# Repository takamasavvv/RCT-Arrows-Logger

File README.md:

# RCT-Arrows-Logger
 Logger module for GS-8

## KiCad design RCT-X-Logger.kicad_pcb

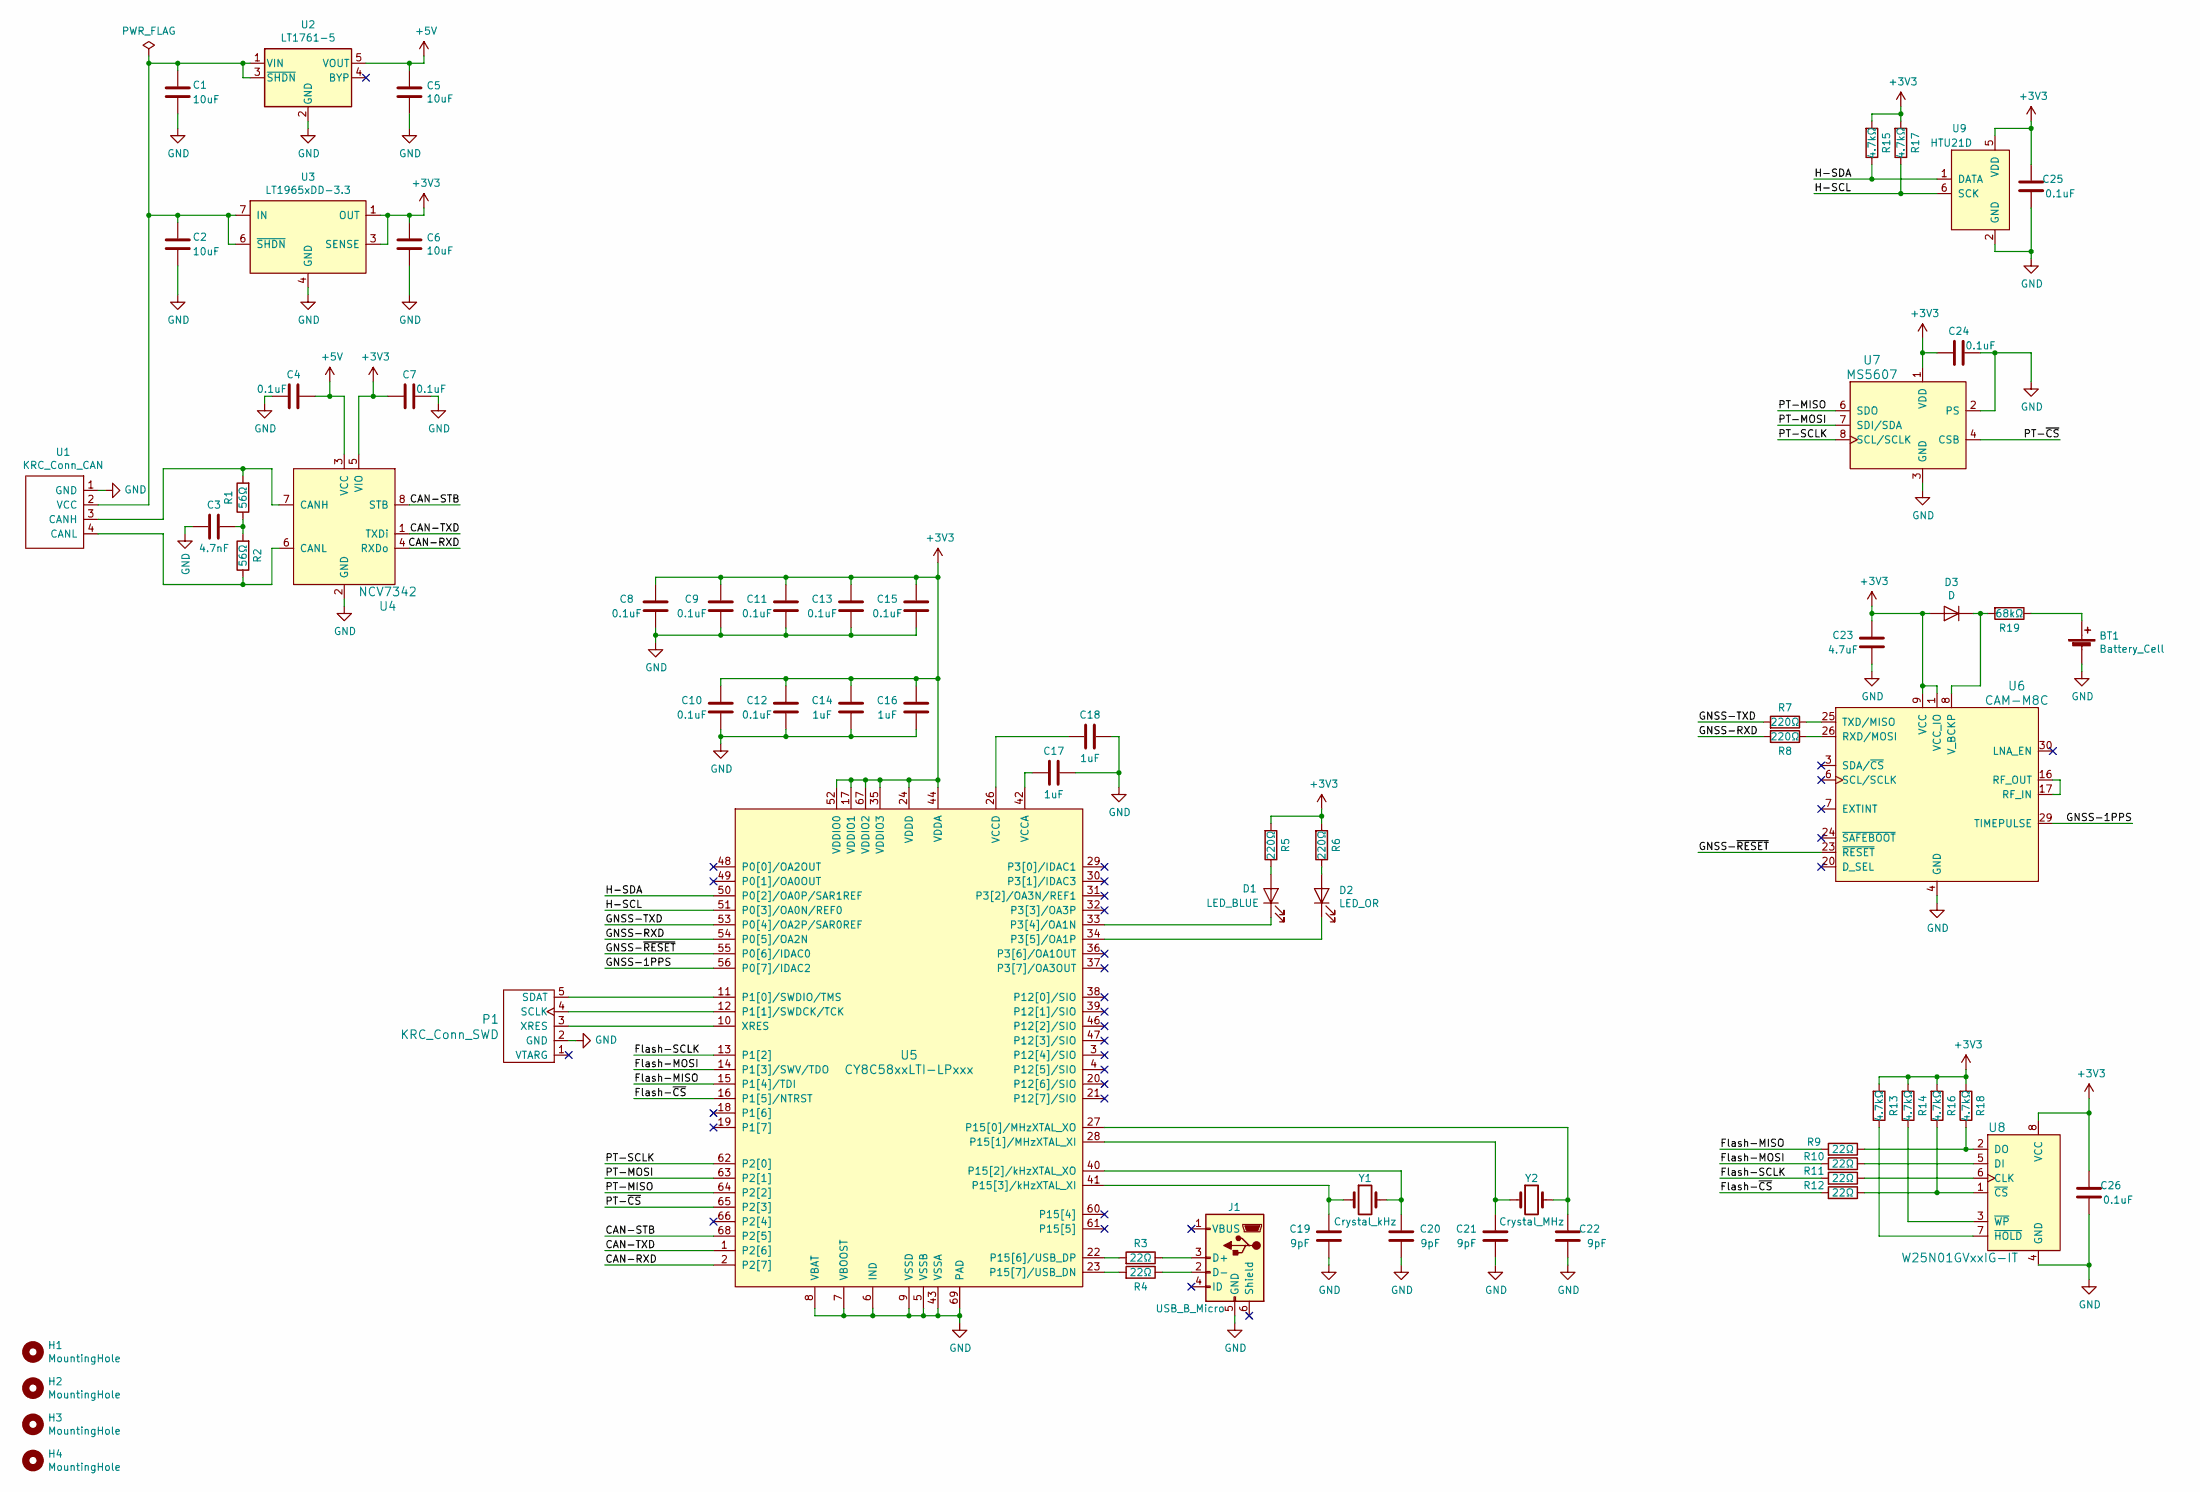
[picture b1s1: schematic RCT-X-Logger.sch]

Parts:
BT1: Battery_Cell; BatteryHolder_Seiko_MS621F; MPN MS621FE
C1, C2, C5, C6: 10uF; C_0603_1608Metric; MPN GRM188R61E106MA73D
C3: 4.7nF; C_0402_1005Metric; MPN GRM155R71H472KA01D
C4, C7, C8, C9, C10, C11, C12, C13, C15, C24, C25, C26: 0.1uF; C_0402_1005Metric; MPN GRM155R62A104KE14D
C14, C16, C17, C18: 1uF; C_0402_1005Metric; MPN GRM155R61E105KA12D
C19, C20, C21, C22: 9pF; C_0201_0603Metric; MPN GRM0335C1E9R0CA01D
C23: 4.7uF; C_0603_1608Metric; MPN GRM185R61C475ME11D
D1: LED_BLUE; LED_0603_1608Metric; MPN SMLE12BC7TT86
D2: LED_OR; LED_0603_1608Metric; MPN SML-E12D8WT86
D3: D; D_SOD-723; MPN 1SS400GT2R
H1, H2, H3, H4: MountingHole; MountingHole_3.5mm
J1: USB_B_Micro; Hirose_ZX_ZX62D-B-5P8; MPN ZX62D-B-5P8(30)
P1: KRC_Conn_SWD; JST_JQ_05JQ-BT_1x05_P2.5mm_Vertical; MPN 05JQ-BT
R1, R2: 56Ω; R_0402_1005Metric; MPN ERJ-2GEJ560X
R3, R4, R9, R10, R11, R12: 22Ω; R_0402_1005Metric; MPN ERJ-2GEJ220X
R5, R6, R7, R8: 220Ω; R_0402_1005Metric; MPN ERJ-2GEJ221X
R13, R14, R15, R16, R17, R18: 4.7kΩ; R_0402_1005Metric; MPN ERJ-2GEJ472X
R19: 68kΩ; R_0402_1005Metric; MPN ERJ-2GEJ683X
U1: KRC_Conn_CAN; JST_XH_S4B-XH-A_1x04_P2.50mm_Horizontal; MPN S4B-XH-A
U2: LT1761-5; TSOT-23-5; MPN LT1761MPS5-5#TRMPBF
U3: LT1965xDD-3.3; DFN-8-1EP_3x3mm_P0.5mm_EP1.66x2.38mm; MPN LT1965EDD-3.3#PBF
U4: NCV7342; DFN-8-1EP_3x3mm_P0.65mm_EP1.55x2.4mm; MPN NCV7342MW3R2G
U5: CY8C58xxLTI-LPxxx; Cypress_QFN-68_EP_8x8_Pitch0.4mm; MPN CY8C5868LTI-LP039
U6: CAM-M8C; ublox-CAM; MPN CAM-M8C-0-10
U7: MS5607; TE_Sensor_MS8607; MPN MS560702BA03-50
U8: W25N01GVxxIG-IT; WSON-8_8x6mm_P1.27mm; MPN W25N01GVZEIG TR
U9: HTU21D; DFN-6-1EP_3x3mm_P1mm_EP1.5x2.4mm; MPN HPP845E131R4
Y1: Crystal_kHz; Crystal_SeikoEpson_FC-135; MPN FC-135R 32.7680KF-AC3
Y2: Crystal_MHz; Crystal_Murata_XRCHA; MPN XRCHA24M000F0A01R0

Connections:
+3V3: C6.1, C7.1, C8.2, C9.2, C10.2, C11.2, C12.2, C13.2, C14.1, C15.2, C16.1, C23.2, C24.2, C25.2, C26.2, D3.2 (A), R5.2, R6.2, R13.2, R14.2, R15.2, R16.2, R17.2, R18.2, U3.1 (OUT), U3.2 (OUT), U3.3 (SENSE), U4.5 (VIO), U5.17 (VDDIO1), U5.24 (VDDD), U5.35 (VDDIO3), U5.44 (VDDA), U5.52 (VDDIO0), U5.59 (VDDD), U5.67 (VDDIO2), U6.1 (VCC_IO), U6.9 (VCC), U7.1 (VDD), U8.8 (VCC), U9.5 (VDD)
+5V: C4.1, C5.1, U2.5 (VOUT), U4.3 (VCC)
/CAN-RXD: U4.4 (RXDo), U5.2 (P2[7])
/CAN-STB: U4.8 (STB), U5.68 (P2[5])
/CAN-TXD: U4.1 (TXDi), U5.1 (P2[6])
/Flash-MISO: R9.2, U5.15 (P1[4]/TDI)
/Flash-MOSI: R10.2, U5.14 (P1[3]/SWV/TDO)
/Flash-SCLK: R11.2, U5.13 (P1[2])
/Flash-~CS: R12.2, U5.16 (P1[5]/NTRST)
/GNSS-1PPS: U5.56 (P0[7]/IDAC2), U6.29 (TIMEPULSE)
/GNSS-RXD: R8.2, U5.54 (P0[5]/OA2N)
/GNSS-TXD: R7.2, U5.53 (P0[4]/OA2P/SAR0REF)
/GNSS-~RESET: U5.55 (P0[6]/IDAC0), U6.23 (~RESET)
/H-SCL: R17.1, U5.51 (P0[3]/OA0N/REF0), U9.6 (SCK)
/H-SDA: R15.1, U5.50 (P0[2]/OA0P/SAR1REF), U9.1 (DATA)
/PT-MISO: U5.64 (P2[2]), U7.6 (SDO)
/PT-MOSI: U5.63 (P2[1]), U7.7 (SDI/SDA)
/PT-SCLK: U5.62 (P2[0]), U7.8 (SCL/SCLK)
/PT-~CS: U5.65 (P2[3]), U7.4 (CSB), U7.5 (CSB)
GND: BT1.2 (-), C1.2, C2.2, C3.2, C4.2, C5.2, C6.2, C7.2, C8.1, C9.1, C10.1, C11.1, C12.1, C13.1, C14.2, C15.1, C16.2, C17.2, C18.2, C19.1, C20.1, C21.1, C22.1, C23.1, C24.1, C25.1, C26.1, J1.5 (GND), P1.2 (GND), U1.1 (GND), U2.2 (GND), U3.4 (GND), U3.5 (GND), U3.9 (PAD), U4.2 (GND), U4.9 (PAD), U5.5 (VSSB), U5.6 (IND), U5.7 (VBOOST), U5.8 (VBAT), U5.9 (VSSD), U5.25 (VSSD), U5.43 (VSSA), U5.45 (VSSD), U5.58 (VSSD), U5.69 (PAD), U6.4 (GND), U6.5 (GND), U6.10 (GND), U6.11 (GND), U6.12 (GND), U6.13 (GND), U6.14 (GND), U6.15 (GND), U6.18 (GND), U6.19 (GND), U6.21 (GND), U6.22 (GND), U6.27 (GND), U6.31 (GND), U7.2 (PS), U7.3 (GND), U8.4 (GND), U8.9 (PAD), U9.2 (GND), U9.7 (PAD)
unnamed: BT1.1 (+), R19.1
unnamed: C1.1, C2.1, U1.2 (VCC), U2.1 (VIN), U2.3 (~SHDN), U3.6 (~SHDN), U3.7 (IN), U3.8 (IN)
unnamed: C3.1, R1.1, R2.2
unnamed: C17.1, U5.42 (VCCA)
unnamed: C18.1, U5.26 (VCCD), U5.57 (VCCD)
unnamed: C19.2, U5.41 (P15[3]/kHzXTAL_XI), Y1.1
unnamed: C20.2, U5.40 (P15[2]/kHzXTAL_XO), Y1.2
unnamed: C21.2, U5.28 (P15[1]/MHzXTAL_XI), Y2.1
unnamed: C22.2, U5.27 (P15[0]/MHzXTAL_XO), Y2.2
unnamed: D1.1 (K), U5.33 (P3[4]/OA1N)
unnamed: D1.2 (A), R5.1
unnamed: D2.1 (K), U5.34 (P3[5]/OA1P)
unnamed: D2.2 (A), R6.1
unnamed: D3.1 (K), R19.2, U6.8 (V_BCKP)
unnamed: J1.2 (D-), R4.1
unnamed: J1.3 (D+), R3.1
unnamed: P1.3 (XRES), U5.10 (XRES)
unnamed: P1.4 (SCLK), U5.12 (P1[1]/SWDCK/TCK)
unnamed: P1.5 (SDAT), U5.11 (P1[0]/SWDIO/TMS)
unnamed: R1.2, U1.3 (CANH), U4.7 (CANH)
unnamed: R2.1, U1.4 (CANL), U4.6 (CANL)
unnamed: R3.2, U5.22 (P15[6]/USB_DP)
unnamed: R4.2, U5.23 (P15[7]/USB_DN)
unnamed: R7.1, U6.25 (TXD/MISO)
unnamed: R8.1, U6.26 (RXD/MOSI)
unnamed: R10.1, U8.5 (DI)
unnamed: R11.1, U8.6 (CLK)
unnamed: R12.1, R16.1, U8.1 (~CS)
unnamed: R13.1, U8.7 (~HOLD)
unnamed: R14.1, U8.3 (~WP)
unnamed: R9.1, R18.1, U8.2 (DO)
unnamed: U6.16 (RF_OUT), U6.17 (RF_IN)

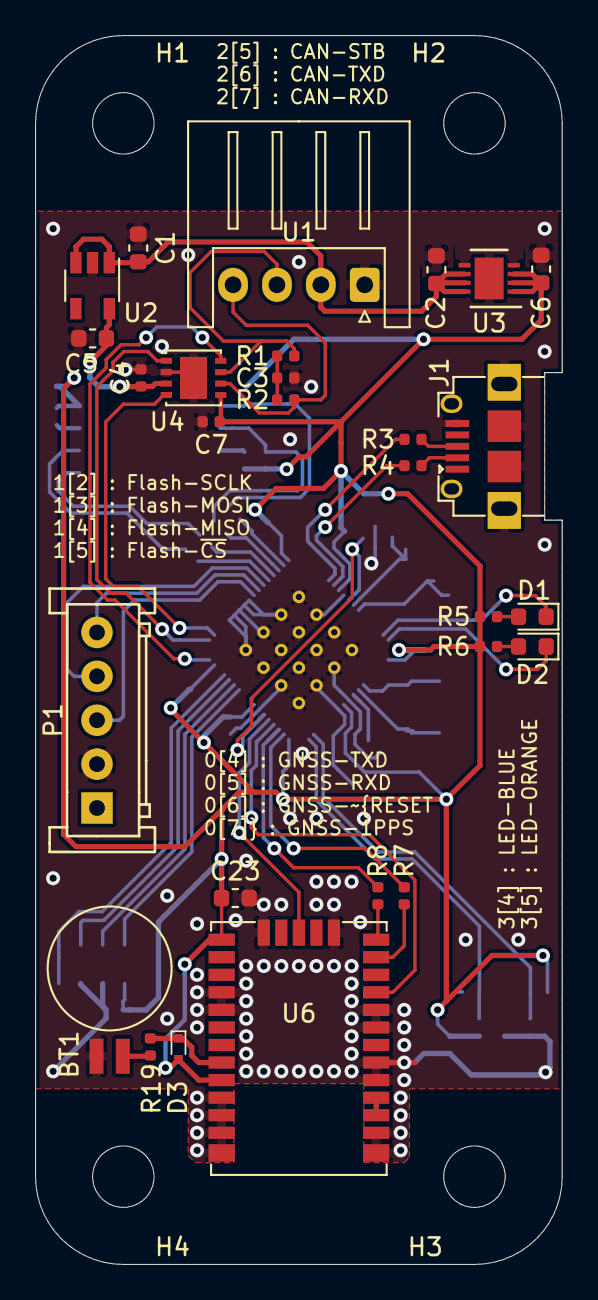
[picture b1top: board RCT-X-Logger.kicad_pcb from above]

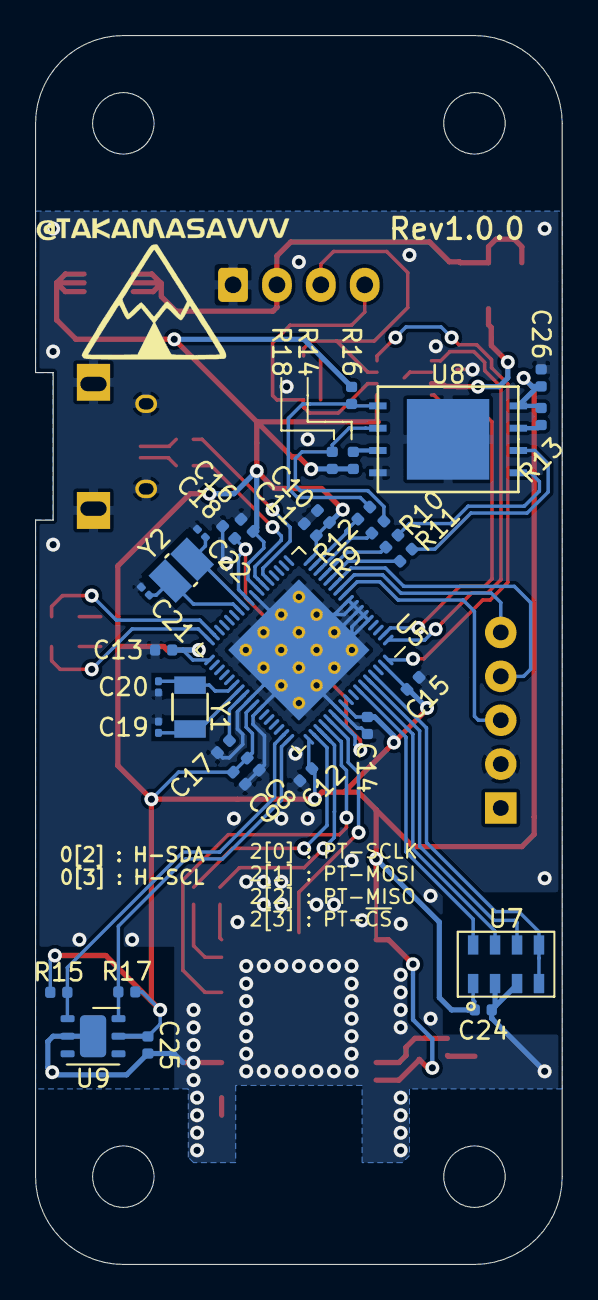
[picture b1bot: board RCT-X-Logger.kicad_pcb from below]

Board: 2 copper layers, 30.0 x 70.0 mm, 66 parts (34 on the bottom side), 52 nets.

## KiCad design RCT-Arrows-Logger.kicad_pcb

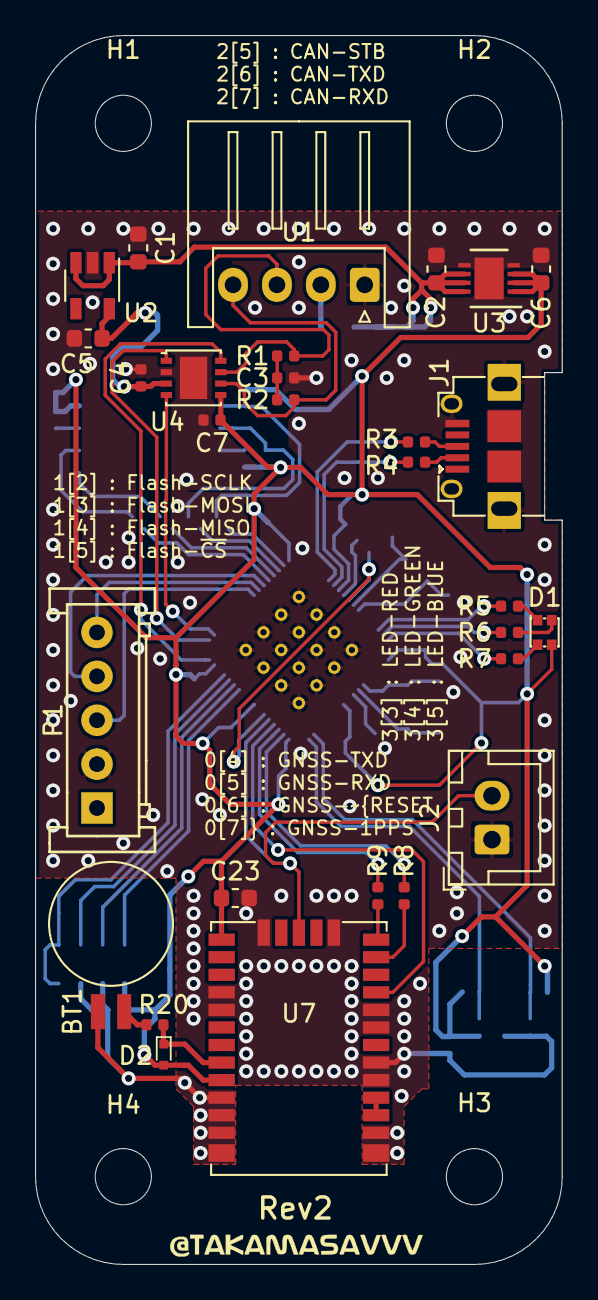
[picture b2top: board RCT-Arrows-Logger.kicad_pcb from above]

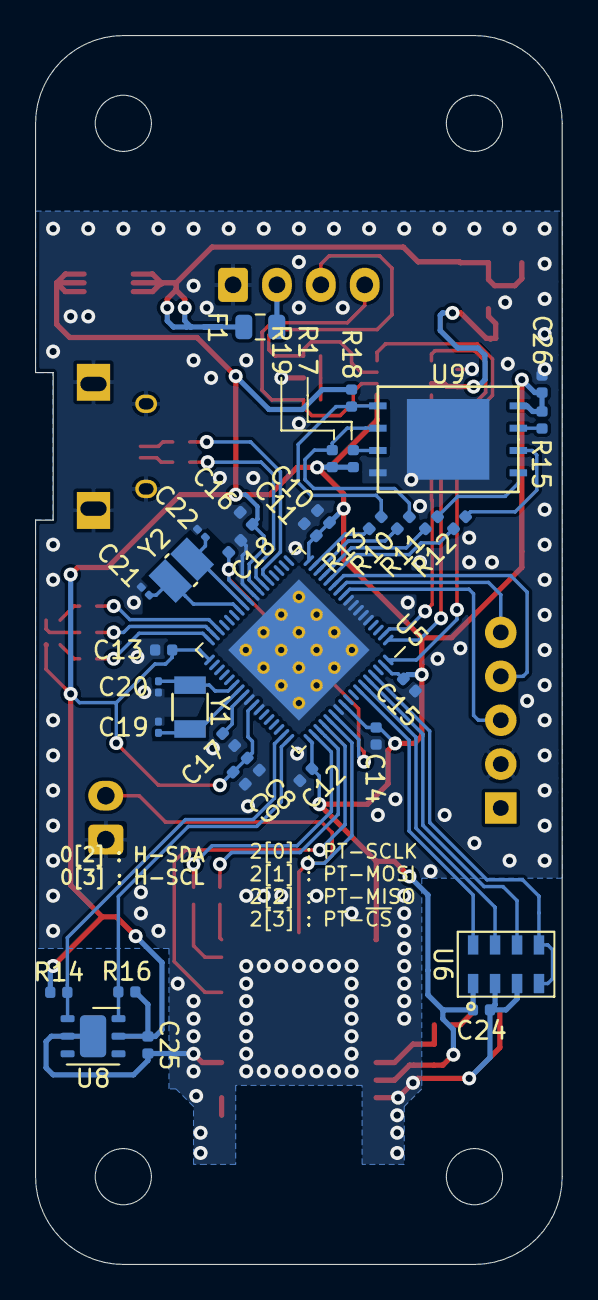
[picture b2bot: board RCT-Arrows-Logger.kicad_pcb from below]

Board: 2 copper layers, 30.0 x 70.0 mm, 68 parts (35 on the bottom side), 55 nets.

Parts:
BT1: Battery_Cell; BatteryHolder_Seiko_MS621F
C1, C2, C5, C6: 10uF; C_0603_1608Metric
C3: 4.7nF; C_0402_1005Metric
C4, C7, C8, C9, C10, C11, C12, C13, C15, C24, C25, C26: 0.1uF; C_0402_1005Metric
C14, C16, C17, C18: 1uF; C_0402_1005Metric
C19, C20, C21, C22: 9pF; C_0201_0603Metric
C23: 4.7uF; C_0603_1608Metric
D1: LED_RGBA; LED_LiteOn_LTST-C19HE1WT
D2: D; D_SOD-723
F1: Polyfuse; Fuse_0805_2012Metric
H1, H2, H3, H4: MountingHole; MountingHole_3.2mm_M3
J1: USB_B_Micro; Hirose_ZX_ZX62D-B-5P8
J2: Conn_01x02; JST_XH_B2B-XH-A_1x02_P2.50mm_Vertical
P1: KRC_Conn_SWD; JST_JQ_05JQ-BT_1x05_P2.5mm_Vertical
R1, R2: 56Ω; R_0402_1005Metric
R3, R4, R8, R9, R10, R11, R12, R13: 22Ω; R_0402_1005Metric
R5: 1.5kΩ; R_0402_1005Metric
R6, R7: 820Ω; R_0402_1005Metric
R14, R15, R16, R17, R18, R19: 4.7kΩ; R_0402_1005Metric
R20: 68kΩ; R_0402_1005Metric
U1: KRC_Conn_CAN; JST_XH_S4B-XH-A_1x04_P2.50mm_Horizontal
U2: LT1761-5; TSOT-23-5
U3: LT1965xDD-3.3; DFN-8-1EP_3x3mm_P0.5mm_EP1.66x2.38mm
U4: NCV7342; DFN-8-1EP_3x3mm_P0.65mm_EP1.55x2.4mm
U5: CY8C58xxLTI-LPxxx; Cypress_QFN-68_EP_8x8_Pitch0.4mm
U6: MS5611; TE_Sensor_MS8607
U7: CAM-M8C; ublox-CAM
U8: HTU21D; DFN-6-1EP_3x3mm_P1mm_EP1.5x2.4mm
U9: W25N01GVxxIG-IT; WSON-8_8x6mm_P1.27mm
Y1: Crystal_kHz; Crystal_SeikoEpson_FC-135
Y2: Crystal_MHz; Crystal_Murata_XRCHA

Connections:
+3V3: C6.1, C7.1, C8.2, C9.2, C10.2, C11.2, C12.2, C13.2, C14.1, C15.2, C16.1, C23.2, C24.2, C25.2, C26.2, D1.4, D2.2, R14.2, R15.2, R16.2, R17.2, R18.2, R19.2, U3.1, U3.2, U3.3, U4.5, U5.17, U5.24, U5.35, U5.44, U5.52, U5.59, U5.67, U6.1, U7.1, U7.9, U8.5, U9.8
+5V: C4.1, C5.1, U2.5, U4.3
/CAN-RXD: U4.4, U5.2
/CAN-STB: U4.8, U5.68
/CAN-TXD: U4.1, U5.1
/Flash-MISO: R10.2, U5.15
/Flash-MOSI: R11.2, U5.14
/Flash-SCLK: R12.2, U5.13
/Flash-~CS: R13.2, U5.16
/GNSS-1PPS: J2.2, U5.56, U7.29
/GNSS-RXD: R9.2, U5.54
/GNSS-TXD: R8.2, U5.53
/GNSS-~RESET: U5.55, U7.23
/H-SCL: R16.1, U5.51, U8.6
/H-SDA: R14.1, U5.50, U8.1
/PT-MISO: U5.64, U6.6
/PT-MOSI: U5.63, U6.7
/PT-SCLK: U5.62, U6.8
/PT-~CS: U5.65, U6.4, U6.5
GND: BT1.2, C1.2, C2.2, C3.2, C4.2, C5.2, C6.2, C7.2, C8.1, C9.1, C10.1, C11.1, C12.1, C13.1, C14.2, C15.1, C16.2, C17.2, C18.2, C19.1, C20.1, C21.1, C22.1, C23.1, C24.1, C25.1, C26.1, J1.5, J2.1, P1.2, U1.1, U2.2, U3.4, U3.5, U3.9, U4.2, U4.9, U5.5, U5.6, U5.7, U5.8, U5.9, U5.25, U5.43, U5.45, U5.58, U5.69, U6.2, U6.3, U7.4, U7.5, U7.10, U7.11, U7.12, U7.13, U7.14, U7.15, U7.18, U7.19, U7.21, U7.22, U7.27, U7.31, U8.2, U8.7, U9.4, U9.9
unnamed: BT1.1, R20.1
unnamed: C1.1, C2.1, F1.1, U2.1, U2.3, U3.6, U3.7, U3.8
unnamed: C3.1, R1.1, R2.2
unnamed: C17.1, U5.42
unnamed: C18.1, U5.26, U5.57
unnamed: C19.2, U5.41, Y1.1
unnamed: C20.2, U5.40, Y1.2
unnamed: C21.2, U5.28, Y2.1
unnamed: C22.2, U5.27, Y2.2
unnamed: D1.1, R5.2
unnamed: D1.2, R6.2
unnamed: D1.3, R7.2
unnamed: D2.1, R20.2, U7.8
unnamed: F1.2, U1.2
unnamed: J1.2, R4.1
unnamed: J1.3, R3.1
unnamed: P1.3, U5.10
unnamed: P1.4, U5.12
unnamed: P1.5, U5.11
unnamed: R1.2, U1.3, U4.7
unnamed: R2.1, U1.4, U4.6
unnamed: R3.2, U5.22
unnamed: R4.2, U5.23
unnamed: R5.1, U5.32
unnamed: R6.1, U5.33
unnamed: R7.1, U5.34
unnamed: R8.1, U7.25
unnamed: R9.1, U7.26
unnamed: R10.1, R19.1, U9.2
unnamed: R11.1, U9.5
unnamed: R12.1, U9.6
unnamed: R13.1, R18.1, U9.1
unnamed: R15.1, U9.7
unnamed: R17.1, U9.3
unnamed: U7.16, U7.17

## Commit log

2019-09-06 MountingHole追加
2019-09-09 [update] 回路初版完成, 部品決定
2019-09-09 [update] 部品追記
2019-09-12 アートワークに合わせて配線変更
2019-09-12 アートワーク完成
2019-09-12 [add] sch svg image
2019-09-12 [add]wrote pin asign and logo
2019-09-12 [update]moved ref name (PSoC 5)
2019-09-12 [add] explain added
2019-09-12 [update] complete v1.0.0
2019-09-12 [update]add enter
2019-09-12 [update]add dir svg/
2019-09-12 [update]add size
2019-09-17 [update]moved capacitor placement
2019-10-10 Completed Rev2
2019-10-29 rename project
